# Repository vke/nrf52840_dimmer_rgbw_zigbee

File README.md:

--- Russian version below ---

# Steps to compile:

* download and install Segger Embedded Studio for ARM (SES) - free for Nodric Semiconductor hardware users
* download and unpack into any directory Nordic Semiconductor's ZigBee SDK 4.2.0
* download (clone) this repository into `\examples\zigbee\vke\nrf52840_dimmer_rgbw` of unpacked ZigBee SDK. main.c file should be located at `\examples\zigbee\vke\nrf52840_dimmer_rgbw\main.c`
* open `\examples\zigbee\vke\nrf52840_dimmer_rgbw\efekta_mini_dev_board\mbr\ses\nrf52840_dimmer_rgbw_mbr.emProject` project file in SES
* click on Build => Build nrf52840_dimmer_rgbw_mbr menu item inside SES to build project
* hex files for manual firmware download will be available at `\examples\zigbee\vke\nrf52840_dimmer_rgbw\efekta_mini_dev_board\mbr\ses\Output` subdirectories depending on Release/Debug setting and so on
* if you have J-Link connected you can simply click on Build => Build and run or Build => Build and debug menu items.
* please be careful - the project is not yet complete and may contain serious bugs.

# Что нужно сделать, чтобы скомпилировать и запустить пример:

* скачать и установить Segger Embedded Studio for ARM (SES) - бесплатно для чипов от Nordic Semiconductor
* скачать и распаковать в любую директорию ZigBee SDK 4.2.0 с сайта Nordic Semiconductor
* скачать (или склонировать) этот репозитарий в директорию `\examples\zigbee\vke\nrf52840_dimmer_rgbw` от ZigBee SDK 4 так, чтобы файл main.c был по пути `\examples\zigbee\vke\nrf52840_dimmer_rgbw\main.c`
* открыть проект `\examples\zigbee\vke\nrf52840_dimmer_rgbw\efekta_mini_dev_board\mbr\ses\nrf52840_dimmer_rgbw_mbr.emProject` внутри SES
* нажать на Build => Build nrf52840_dimmer_rgbw_mbr в меню SES для сборки проекта
* hex-файлы для самостоятельной прошивки будут доступны в директории `\examples\zigbee\vke\nrf52840_dimmer_rgbw\efekta_mini_dev_board\mbr\ses\Output` в поддиректориях, соответствующих конфигурации (Release/Debug)
* если подключен дебаггер J-Link, то достаточно нажать в меню на Build => Build and run или Build => Build and debug, чтобы запустить прошивку
* пожалуйста, будьте осторожны - проект еще не закончен и может содержать серьёзные ошибки.

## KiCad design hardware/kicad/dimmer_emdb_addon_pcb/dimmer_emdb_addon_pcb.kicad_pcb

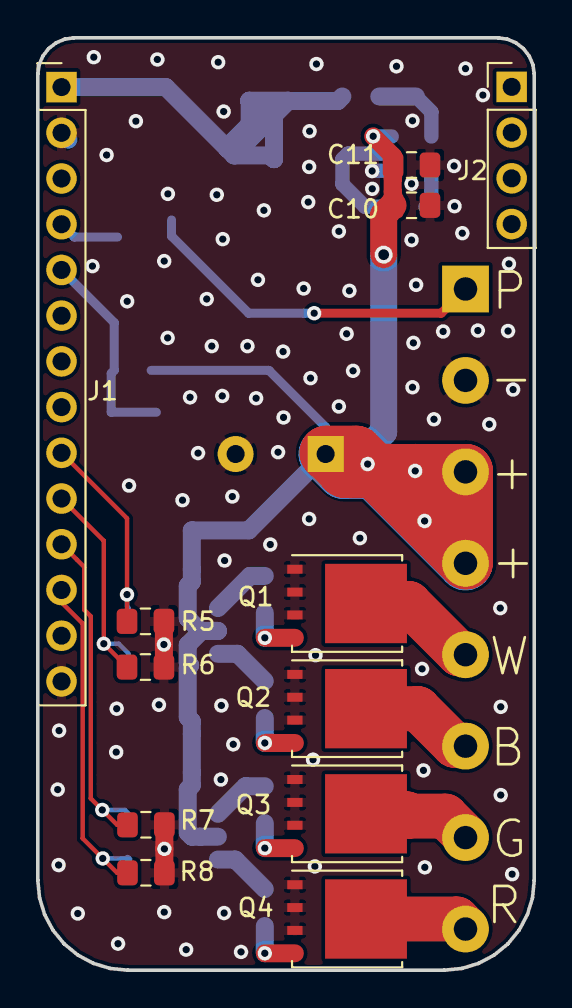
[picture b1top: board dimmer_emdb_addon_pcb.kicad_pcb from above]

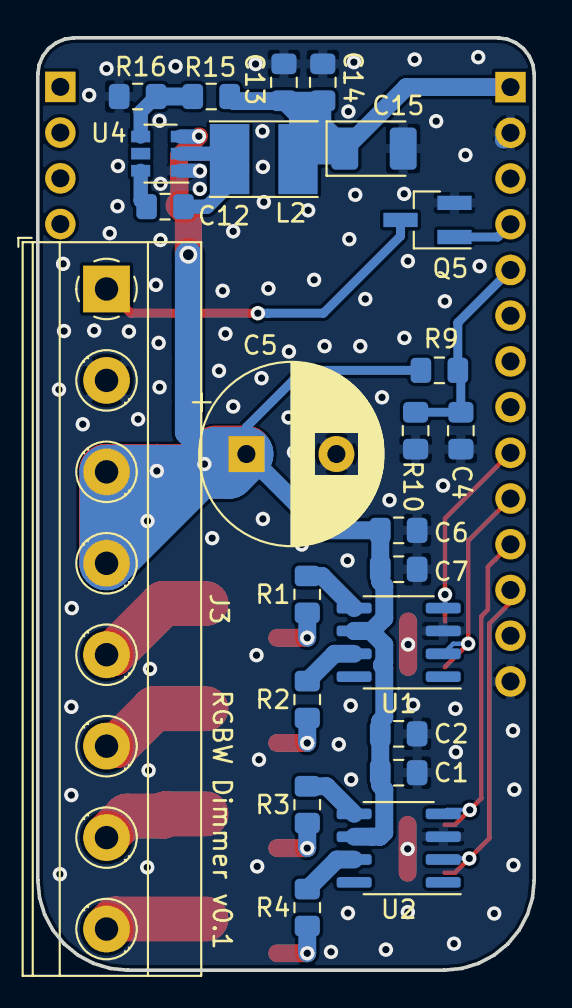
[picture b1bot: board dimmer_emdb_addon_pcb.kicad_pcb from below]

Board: 2 copper layers, 27.6 x 51.8 mm, 36 parts (24 on the bottom side), 25 nets.

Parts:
C1, C6, C10, C14: 4.7uF; C_0805_2012Metric_Pad1.15x1.40mm_HandSolder
C2, C7, C11, C12, C13: 0.1uF; C_0805_2012Metric_Pad1.15x1.40mm_HandSolder
C4: 1uF; C_0805_2012Metric_Pad1.15x1.40mm_HandSolder
C5: 100uF; CP_Radial_D10.0mm_P5.00mm
C15: 47uF; CP_EIA-3528-21_Kemet-B_Pad1.50x2.35mm_HandSolder
J1: Conn_01x14_Male; Pin_Header_Straight_1x14_Pitch2.54mm
J2: Conn_01x04_Male; PinHeader_1x04_P2.54mm_Vertical
J3: Screw_Terminal_01x08; TerminalBlock_Phoenix_MKDS-1,5-8-5.08_1x08_P5.08mm_Horizont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
L2: 10uH; L_Taiyo-Yuden_NR-40xx_HandSoldering
Q1, Q2, Q3, Q4: BSC067N06LS3G; TDSON-8-1
Q5: LMUN2233LT1G; SOT-23_Handsoldering
R1, R2, R3, R4: 50R; R_0805_2012Metric_Pad1.15x1.40mm_HandSolder
R5, R6, R7, R8: 10K; R_0805_2012Metric_Pad1.15x1.40mm_HandSolder
R9, R15: 100K; R_0805_2012Metric_Pad1.15x1.40mm_HandSolder
R10: 22K; R_0805_2012Metric_Pad1.15x1.40mm_HandSolder
R16: 22K1; R_0805_2012Metric_Pad1.15x1.40mm_HandSolder
U1, U2: TC4427; SOIC-8_3.9x4.9mm_P1.27mm
U4: TPS54202DDCR; SOT-23-6

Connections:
12V_Sense: C4.1, J1.5, R9.2, R10.1
+3V3: C13.1, C14.1, C15.1, J1.1, L2.2, R15.1
+12V: C1.1, C2.1, C5.1, C6.1, C7.1, C10.1, C11.1, J3.3, J3.4, R9.1, U1.6, U2.6, U4.3
/B_IN: J1.10, R6.1, U1.2
/B_OUT: J3.6, Q2.5
/G_IN: J1.11, R7.1, U2.4
/G_OUT: J3.7, Q3.5
/NET_BOOT: C12.2, U4.6
/NET_FB: R15.2, R16.1, U4.4
/NET_SW: C12.1, L2.1, U4.2
/PSU_ENABLE_OUT: J3.1, Q5.3
/R_IN: J1.12, R8.1, U2.2
/R_OUT: J3.8, Q4.5
/W_IN: J1.9, R5.1, U1.4
/W_OUT: J3.5, Q1.5
GND: C1.2, C2.2, C4.2, C5.2, C6.2, C7.2, C10.2, C11.2, C13.2, C14.2, C15.2, J1.2, J1.14, J3.2, Q1.1, Q1.2, Q1.3, Q2.1, Q2.2, Q2.3, Q3.1, Q3.2, Q3.3, Q4.1, Q4.2, Q4.3, Q5.2, R5.2, R6.2, R7.2, R8.2, R10.2, R16.2, U1.3, U2.3, U4.1
unnamed: Q1.4, R1.1
unnamed: Q2.4, R2.1
unnamed: Q3.4, R3.1
unnamed: Q4.4, R4.1
unnamed: R1.2, U1.5
unnamed: R2.2, U1.7
unnamed: R3.2, U2.5
unnamed: R4.2, U2.7
PSU_Enable: J1.4, Q5.1

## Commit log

2020-02-10 Moved from debug breadboard to Efekta mini dev board White color is ON by default Improved debug logging
2020-02-15 Upgrade to Zigbee SDK 4.0 UART logs are enabled by default Minor file layout optimization Hold user key during (re)start to reset Zigbee memory
2020-02-21 Preliminary OTA support
2020-02-21 Define pins for dimmer daughter board
2020-02-21 Incomplete project warning
2020-02-21 Dimmer addon PCB project for KiCad EDA
2020-03-23 Spelling errors fixed
2020-05-03 v1.2.0.7
2020-07-15 Split hardware and software parts of project, hardware files removed
2022-09-09 Version 1.2.1.0 for Zigbee SDK 4.2.0, incomplete
2022-09-10 Version 1.2.1.1
